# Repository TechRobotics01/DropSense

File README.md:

# DropSense
"what acctually happens when something drops"
dropsense answers that with data 

Dropsense is a wireless embedded system project which logs and transmits data in real time 
what type of data exactly?- it transmits the height from which it is dropped, the time period of the drop and the maximum Gforce which the device accelerated to during the impact .

Basically it consists of two parts the sender and the reciever 

# IMPORTANT POINT FOR THE REVIEWER
PLEASE CONSIDER THIS AS A DIGITAL DESIGN ONLY I DO NOT MEAN TO SUBMIT IT AS A IRL BUILD BUT A DIGITAL 2ND ITERATION OF THE PROJECT 
WHEN I BUILT THIS PROJECT IRL IT DID NOT WORK NOT BECAUSE IT WASN'T DESIGNED PROPERLY BUT BECAUSE AN IC FAILED AND WHICH I AM NOT ABLE TO REPLACE BECAUSE IT IS EXTREMELY COSTLY SO PLEASE CONSIDER THIS AS A DIGITAL DESIGN AND APPROVE IT 

# SENDER 
the sender consists of a custom made pcb which has a an esp32 s3 wroom 1 module an microsd card holder and a mpu6050(smd)
the sender will read the data and log it in sd card module and upomn impact that is g force greater than 5Gs then it will send info about the drop(height,time period etc) to the reciever btw this all is battery operated and it has a custom bms to power the pcb

This devise has hexagonal walls because they are better at abosrbing impacts!

# RECIEVER 
The reciever consists of an esp32 s3 wroom1 module and also an 1.8 inch tft display along with a custom made BMS for charging the battery which powers the pcb 
and the display shows all the info about the drop when it recieves the data fropm the sender 

# IRL BUILD 
## SENDER

## RECIEVER

## ZINE PAGE

# Hardware
This device consists of 
1. MPU6050
2. Esp32-S3 module (not the development board)
3. sd card module 
4. custom BMS circuit
5. A small Li-Ion batter
6. 1.8 inch tft display 

All these parts will be on a custom made PCB whcih will be be enclosed inside a 3D printed case made out of TPU (you may also use PETG or CF-NYLON for added durability)

## THIS DEVICE HAS AN ERROR OF +-1CM FOR HEIGHT WHICH IS AM EXTREMELY LOW ERROR ##

# software
This was designed using the following softwares 

1. **Fusion360** for the 3d designing of the case
2. **KiCad** for the PCB design of this device

## CONTROL LOGIC
  1. in the prototyping stage
  2. The MPU6050 reads the values at a very high speed
  3. and then the valuse are logged into the sd card in a .csv file format
  4. then for prototyping the .csv file was read and analyzed
  5. figured out the threshold values such ad the gForce values which are required for automatic triggering and logging of data
  6. for eg when the device approached near 0 gForce vaklues the device is considered in a freefall and then the mpu605 starts to log the values in the sd card module and when the impact happend and the gForce stabelized at around 1Gfprce we can consider the device is stationary again and the Esp32 enters deep sleep mode again to save battery power
  7. the .csv file can then be used to plot graphs in different types of softwares for crash analysis
  8. also the crutial values such as drop height and maximum gForce of the crashb and the time time from falling to the crash is printed on the screen of the reciever 

## APPLICATIONS 
**this device can be used and applicated in places where gForce or acceleration and decelleration needs to be preciself analyzed**
1. drone crash analysis simply mount this device onto a drone and it will automaticaklly log the data when the drone crashes 
2. it can also be used in car crash analysis
3. this device acts as a black box for analysuis 

# credits (for R&D of this device)
google.com
https://randomnerdtutorials.com/arduino-mpu-6050-accelerometer-gyroscope/
Adafruit (use for taking out the values from mpu6050)
random nerd tutorials 
grabcad for the 3d step files of the tft and micro usb

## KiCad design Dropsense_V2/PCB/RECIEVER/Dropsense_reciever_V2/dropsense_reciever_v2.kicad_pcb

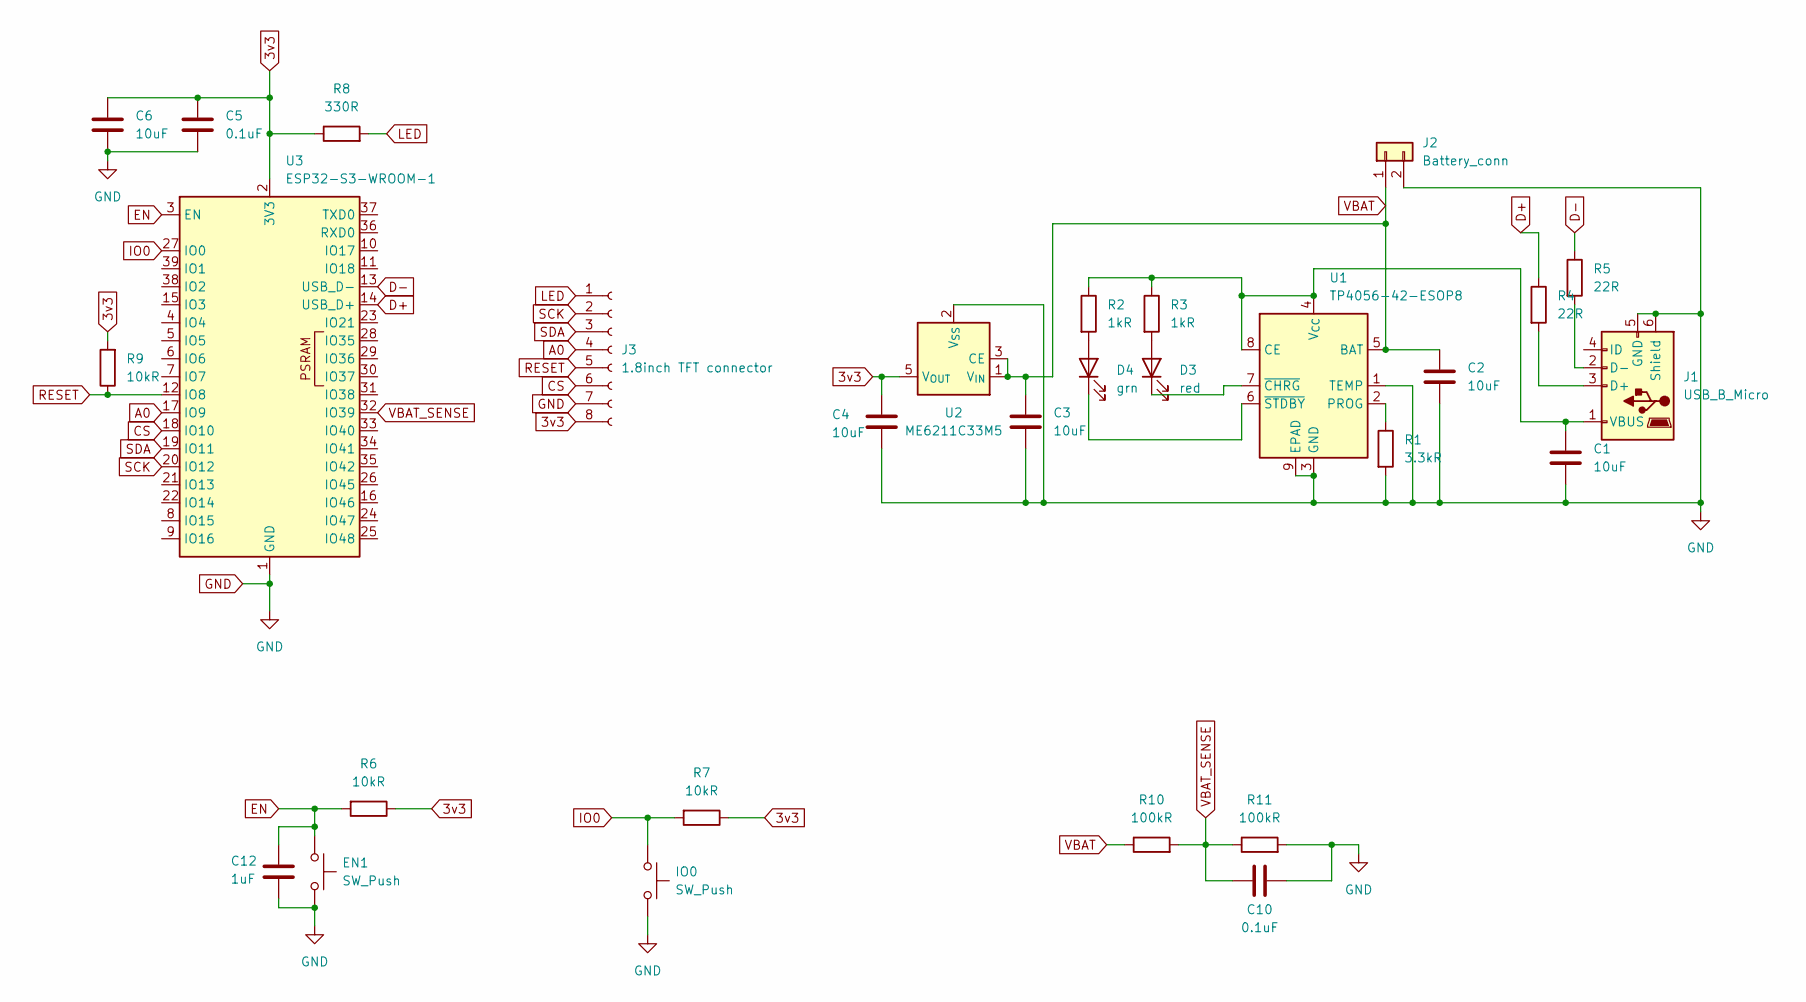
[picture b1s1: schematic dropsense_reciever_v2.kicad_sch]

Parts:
C1, C2, C3, C4, C6: 10uF; C_0805_2012Metric
C5, C10: 0.1uF; C_0805_2012Metric
C12: 1uF; C_0805_2012Metric
D3: red; LED_0805_2012Metric
D4: grn; LED_0805_2012Metric
EN1: SW_Push; SW_Push_1P1T-SH_NO_CK_KMR2xxG
IO0: SW_Push; SW_Push_1P1T-SH_NO_CK_KMR2xxG
J1: USB_B_Micro; USB_Micro-B_Amphenol_10118194-0001LF_Horizontal
J2: Battery_conn; JST_XH_B2B-XH-A_1x02_P2.50mm_Vertical
J3: 1.8inch TFT connector; PinSocket_1x08_P2.54mm_Vertical
R1: 3.3kR; R_0805_2012Metric
R2, R3: 1kR; R_0805_2012Metric
R4, R5: 22R; R_0805_2012Metric
R6, R7, R9: 10kR; R_0805_2012Metric
R8: 330R; R_0805_2012Metric
R10, R11: 100kR; R_0805_2012Metric
U1: TP4056-42-ESOP8; SOIC-8-1EP_3.9x4.9mm_P1.27mm_EP2.41x3.3mm_ThermalVias
U2: ME6211C33M5; SOT-23-5
U3: ESP32-S3-WROOM-1

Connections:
3v3: C4.1, C5.1, C6.1, J3.8, R6.1, R7.1, R8.1, R9.2, U2.5 (V_{OUT}), U3.2 (3V3)
A0: J3.4, U3.17 (IO9)
CS: J3.6, U3.18 (IO10)
D+: R4.1, U3.14 (USB_D+)
D-: R5.1, U3.13 (USB_D-)
EN: C12.1, EN1.1, R6.2, U3.3 (EN)
GND: C1.2, C2.2, C3.2, C4.2, C5.2, C6.2, C10.2, C12.2, EN1.2, IO0.2, J1.5 (GND), J1.6 (Shield), J2.2, J3.7, R1.2, R11.2, U1.1 (TEMP), U1.3 (GND), U1.9 (EPAD), U2.2 (V_{SS}), U3.1 (GND), U3.40 (GND), U3.41 (GND)
IO0: IO0.1, R7.2, U3.27 (IO0)
LED: J3.1, R8.2
unnamed: D3.2 (A), R3.2
unnamed: D3.1 (K), U1.7 (~CHRG)
unnamed: D4.2 (A), R2.2
unnamed: D4.1 (K), U1.6 (~STDBY)
unnamed: J1.3 (D+), R4.2
unnamed: J1.2 (D-), R5.2
unnamed: C1.1, J1.1 (VBUS), R2.1, R3.1, U1.4 (V_{CC}), U1.8 (CE)
unnamed: R1.1, U1.2 (PROG)
RESET: J3.5, R9.1, U3.12 (IO8)
SCK: J3.2, U3.20 (IO12)
SDA: J3.3, U3.19 (IO11)
VBAT: C2.1, C3.1, J2.1, R10.1, U1.5 (BAT), U2.1 (V_{IN}), U2.3 (CE)
VBAT_SENSE: C10.1, R10.2, R11.1, U3.32 (IO39)

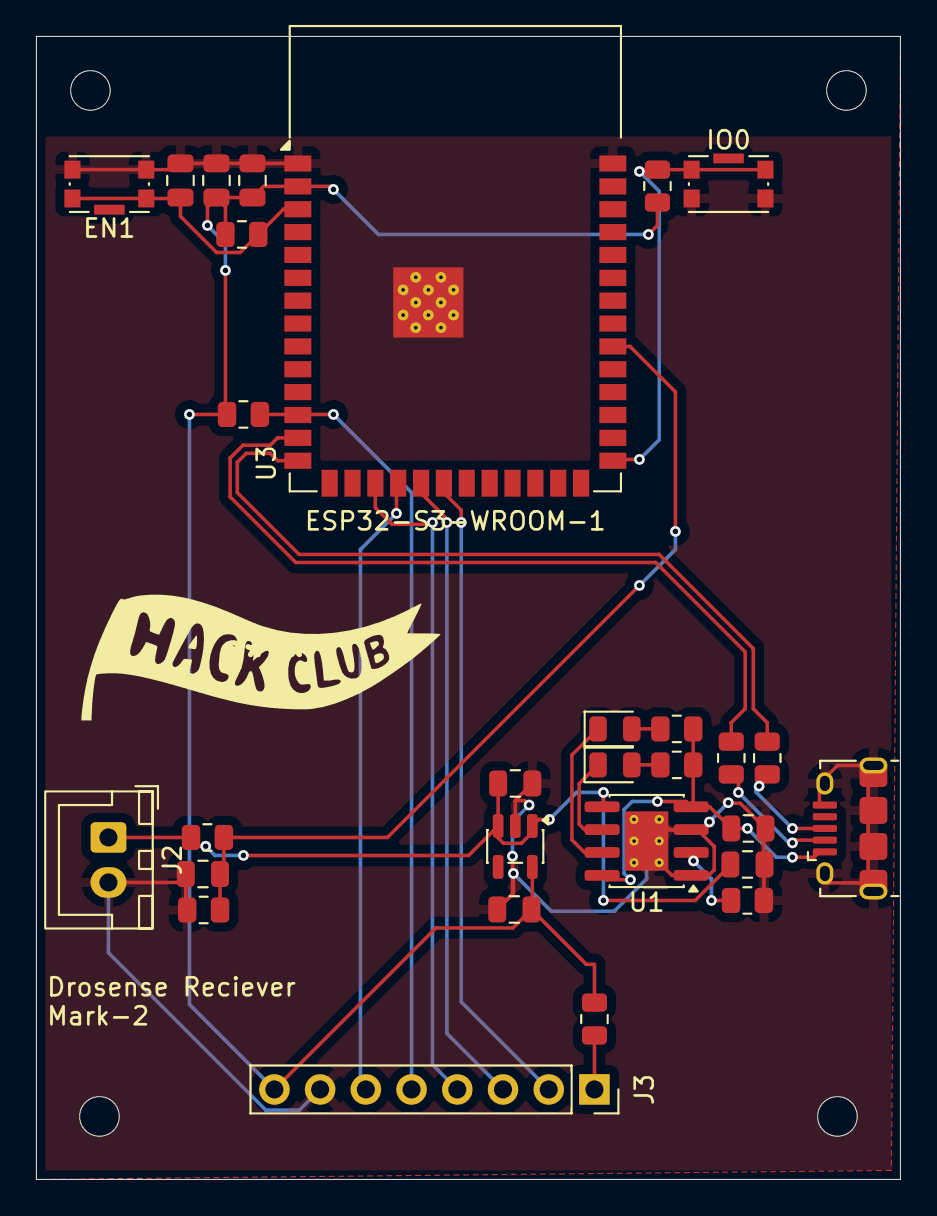
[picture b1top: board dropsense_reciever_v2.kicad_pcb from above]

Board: 2 copper layers, 48.0 x 63.5 mm, 29 parts (0 on the bottom side), 22 nets.

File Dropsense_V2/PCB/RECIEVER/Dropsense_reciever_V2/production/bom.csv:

Designator,Footprint,Quantity,Value,LCSC Part #
"C1, C2, C3, C4, C6",0805,5,10uF,
"C10, C5",0805,2,0.1uF,
C12,0805,1,1uF,
D3,0805,1,red,
D4,0805,1,grn,
"EN1, IO0",SW_Push_1P1T-SH_NO_CK_KMR2xxG,2,SW_Push,
J1,USB_Micro-B_Amphenol_10118194-0001LF_Horizontal,1,USB_B_Micro,
J2,JST_XH_B2B-XH-A_1x02_P2.50mm_Vertical,1,Battery_conn,
J3,PinSocket_1x08_P2.54mm_Vertical,1,1.8inch TFT connector,
R1,0805,1,3.3kR,
"R10, R11",0805,2,100kR,
"R2, R3",0805,2,1kR,
"R4, R5",0805,2,22R,
"R6, R7, R9",0805,3,10kR,
R8,0805,1,330R,
U1,SOIC-8-1EP_3.9x4.9mm_P1.27mm_EP2.41x3.3mm_ThermalVias,1,TP4056-42-ESOP8,
U2,SOT-23-5,1,ME6211C33M5,
U3,ESP32-S3-WROOM-1,1,ESP32-S3-WROOM-1,

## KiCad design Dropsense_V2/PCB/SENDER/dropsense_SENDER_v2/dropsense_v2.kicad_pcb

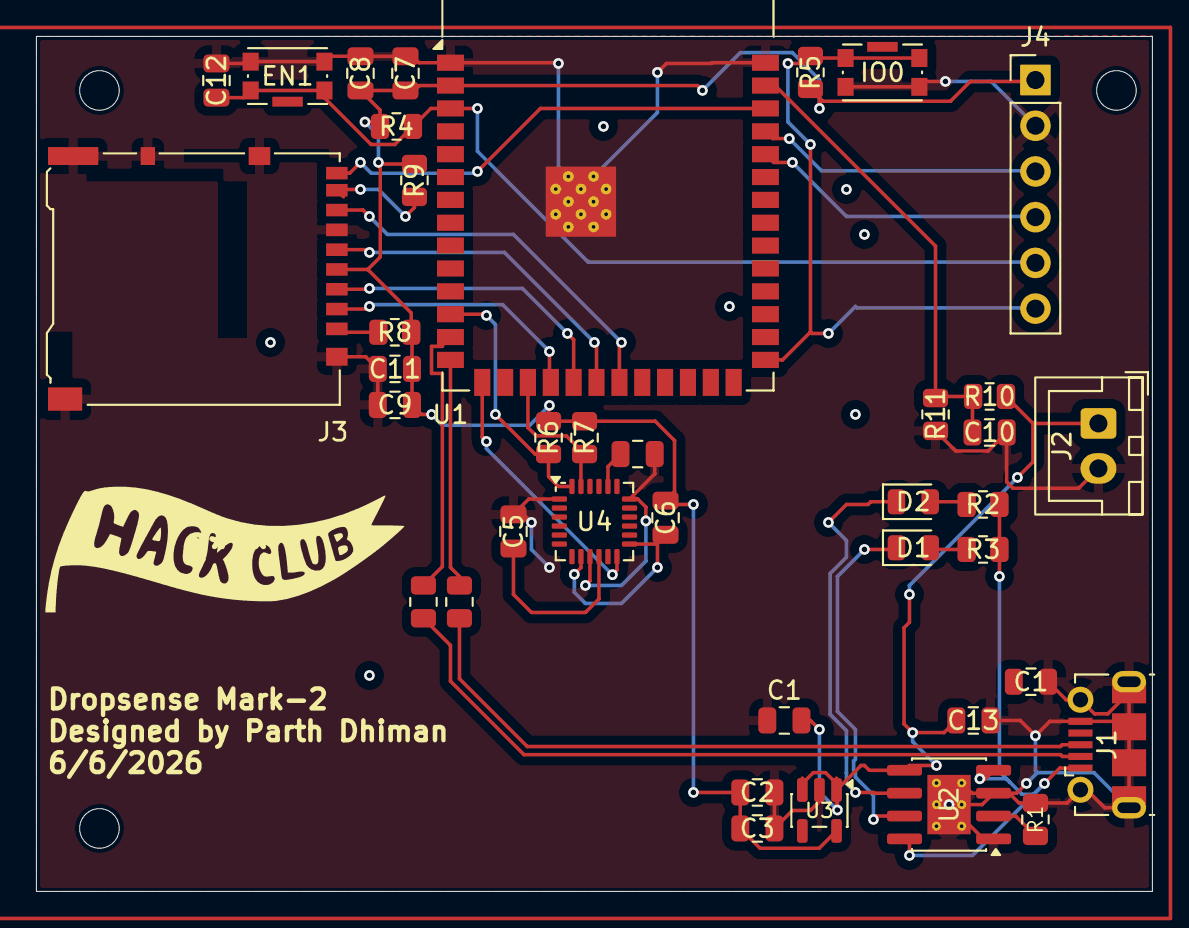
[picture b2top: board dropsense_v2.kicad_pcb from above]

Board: 2 copper layers, 62.0 x 47.5 mm, 39 parts (0 on the bottom side), 31 nets.

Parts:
C1, C1#2, C3, C8, C11, C13: 10uF; C_0805_2012Metric
C2, C6, C7, C9, C10: 0.1uF; C_0805_2012Metric
C4: 2.2nF; C_0805_2012Metric
C5: 100nF; C_0805_2012Metric
C12: 1uF; C_0805_2012Metric
D1: GREEN; LED_0805_2012Metric
D2: RED; LED_0805_2012Metric
EN1: SW_Push; SW_Push_1P1T-SH_NO_CK_KMR2xxG
IO0: SW_Push; SW_Push_1P1T-SH_NO_CK_KMR2xxG
J1: USB_B_Micro; USB_Micro-B_Molex-105017-0001
J2: Conn_01x02; JST_XH_B2B-XH-A_1x02_P2.50mm_Vertical
J3: Micro_SD_Card_Det_Hirose_DM3AT; microSD_HC_Hirose_DM3AT-SF-PEJM5
J4: Conn_01x06_Pin; PinHeader_1x06_P2.54mm_Vertical
R1: 3.3kR; R_0805_2012Metric
R2, R3: 330R; R_0805_2012Metric
R4, R5, R8, R9: 10kR; R_0805_2012Metric
R6, R7: 4.7kR; R_0805_2012Metric
R10, R11: 100kR; R_0805_2012Metric
R12, R13: 22R; R_0805_2012Metric
U1: ESP32-S3-WROOM-1
U2: TP4056-42-ESOP8; SOIC-8-1EP_3.9x4.9mm_P1.27mm_EP2.41x3.3mm_ThermalVias
U3: ME6211C33M5; SOT-23-5
U4: MPU-6050; InvenSense_QFN-24_4x4mm_P0.5mm

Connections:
3V3: C2.1, C3.1, C6.1, C7.1, C8.1, C9.1, C11.1, J3.4 (VDD), J4.1, R4.1, R5.1, R6.1, R7.1, R8.1, R9.1, U1.2 (3V3), U3.5 (V_{OUT})
D+: J1.3 (D+), R13.2
D-: J1.2 (D-), R12.2
EN: C12.1, EN1.1, J4.5, R4.2, U1.3 (EN)
GND: C1.2, C1#2.1, C2.2, C3.2, C4.2, C5.1, C7.2, C8.2, C9.2, C10.2, C11.2, C12.2, C13.2, EN1.2, IO0.2, J1.5 (GND), J1.6 (Shield), J2.2, J3.6 (VSS), J3.10 (DET_A), J3.11 (SHIELD), J4.2, R1.2, R11.2, U1.1 (GND), U1.40 (GND), U1.41 (GND), U2.1 (TEMP), U2.3 (GND), U2.9 (EPAD), U3.2 (V_{SS}), U4.1 (CLKIN), U4.9 (AD0), U4.18 (GND)
IO0: IO0.1, J4.6, R5.2, U1.27 (IO0)
MPU_INTERUPT: U1.15 (IO3), U4.12 (INT)
MPU_SCL: R7.2, U1.17 (IO9), U4.23 (SCL)
MPU_SDA: R6.2, U1.12 (IO8), U4.24 (SDA)
unnamed: D1.2 (A), R3.2
unnamed: D1.1 (K), U2.7 (~CHRG)
unnamed: D2.2 (A), R2.2
unnamed: D2.1 (K), U2.6 (~STDBY)
unnamed: J1.1 (VBUS), R2.1, R3.1, U2.4 (V_{CC}), U2.8 (CE)
unnamed: J3.8 (DAT1), R9.2
unnamed: J3.1 (DAT2), R8.2
unnamed: R13.1, U1.14 (USB_D+)
unnamed: R12.1, U1.13 (USB_D-)
unnamed: R1.1, U2.2 (PROG)
unnamed: C4.1, U4.20 (CPOUT)
unnamed: C5.2, U4.10 (REGOUT)
unnamed: C6.2, U4.8 (VLOGIC), U4.13 (VDD)
RX: J4.4, U1.36 (RXD0)
SD_CS: J3.2 (DAT3/CD), U1.18 (IO10)
SD_DETECT: J3.9 (DET_B), U1.38 (IO2)
SD_MISO: J3.7 (DAT0), U1.21 (IO13)
SD_MOSI: J3.3 (CMD), U1.19 (IO11)
SD_SCK: J3.5 (CLK), U1.20 (IO12)
TX: J4.3, U1.37 (TXD0)
VBAT: C1#2.2, C13.1, J2.1, R10.1, U2.5 (BAT), U3.1 (V_{IN}), U3.3 (CE)
VBAT_SENSE: C10.1, R10.2, R11.1, U1.39 (IO1)

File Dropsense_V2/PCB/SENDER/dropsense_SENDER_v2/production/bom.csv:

Designator,Footprint,Quantity,Value,LCSC Part #
"C1_2, C1, C11, C13, C3, C8",0805,6,10uF,
"C10, C2, C6, C7, C9",0805,5,0.1uF,
C12,0805,1,1uF,
C4,0805,1,2.2nF,
C5,0805,1,100nF,
D1,0805,1,GREEN,
D2,0805,1,RED,
"EN1, IO0",SW_Push_1P1T-SH_NO_CK_KMR2xxG,2,SW_Push,
J1,USB_Micro-B_Molex-105017-0001,1,USB_B_Micro,
J2,JST_XH_B2B-XH-A_1x02_P2.50mm_Vertical,1,Conn_01x02,
J3,microSD_HC_Hirose_DM3AT-SF-PEJM5,1,Micro_SD_Card_Det_Hirose_DM3AT,
J4,PinHeader_1x06_P2.54mm_Vertical,1,Conn_01x06_Pin,
R1,0805,1,3.3kR,
"R10, R11",0805,2,100kR,
"R12, R13",0805,2,22R,
"R2, R3",0805,2,330R,
"R4, R5, R8, R9",0805,4,10kR,
"R6, R7",0805,2,4.7kR,
U1,ESP32-S3-WROOM-1,1,ESP32-S3-WROOM-1,
U2,SOIC-8-1EP_3.9x4.9mm_P1.27mm_EP2.41x3.3mm_ThermalVias,1,TP4056-42-ESOP8,
U3,SOT-23-5,1,ME6211C33M5,
U4,InvenSense_QFN-24_4x4mm_P0.5mm,1,MPU-6050,

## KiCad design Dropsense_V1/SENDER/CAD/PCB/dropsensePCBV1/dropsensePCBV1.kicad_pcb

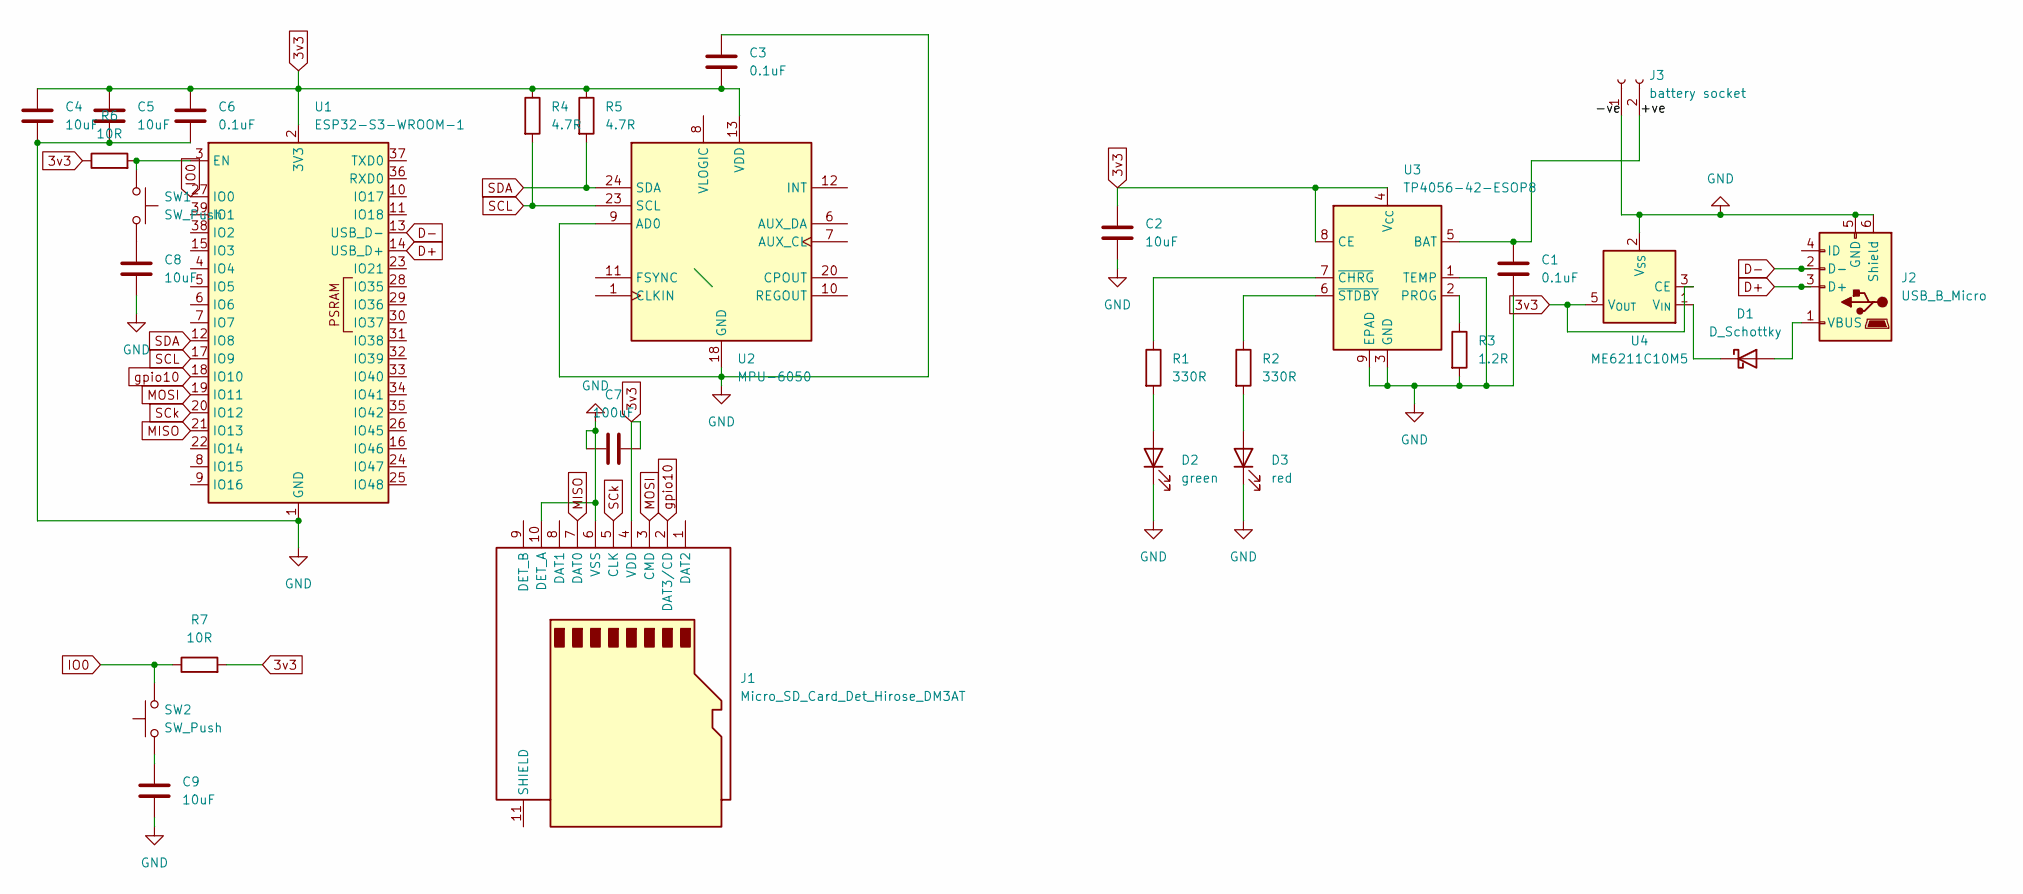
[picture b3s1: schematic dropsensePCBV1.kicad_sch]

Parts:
C1, C3, C6: 0.1uF; C_0805_2012Metric
C2, C4, C5, C8, C9: 10uF; C_0805_2012Metric
C7: 100uF; C_0805_2012Metric
D1: D_Schottky; D_0805_2012Metric
D2: green; LED_0805_2012Metric
D3: red; LED_0805_2012Metric
J1: Micro_SD_Card_Det_Hirose_DM3AT; microSD_HC_Hirose_DM3AT-SF-PEJM5
J2: USB_B_Micro; USB_Micro-B_Amphenol_10103594-0001LF_Horizontal
J3: battery socket; JST_PH_B2B-PH-K_1x02_P2.00mm_Vertical
R1, R2: 330R; R_0805_2012Metric
R3: 1.2R; R_0805_2012Metric
R4, R5: 4.7R; R_0805_2012Metric
R6, R7: 10R; R_0805_2012Metric
SW1, SW2: SW_Push; SW_PUSH_6mm_H4.3mm
U1: ESP32-S3-WROOM-1
U2: MPU-6050; InvenSense_QFN-24_4x4mm_P0.5mm
U3: TP4056-42-ESOP8; SOIC-8-1EP_3.9x4.9mm_P1.27mm_EP2.41x3.3mm_ThermalVias
U4: ME6211C10M5; SOT-23-5

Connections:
3v3: C2.1, C3.2, C4.1, C5.1, C6.1, C7.2, J1.4 (VDD), R4.1, R5.1, R6.1, R7.2, U1.2 (3V3), U2.13 (VDD), U3.4 (V_{CC}), U3.8 (CE), U4.3 (CE), U4.5 (V_{OUT}); also elsewhere on the board
/+ve: C1.1, J3.2, U3.5 (BAT)
D+: J2.3 (D+), U1.14 (USB_D+)
D-: J2.2 (D-), U1.13 (USB_D-)
GND: C1.2, C2.2, C3.1, C4.2, C5.2, C6.2, C7.1, C8.2, C9.2, D2.1 (K), D3.1 (K), J1.6 (VSS), J1.10 (DET_A), J2.5 (GND), J2.6 (Shield), J3.1, R3.2, U1.1 (GND), U1.40 (GND), U1.41 (GND), U2.9 (AD0), U2.18 (GND), U3.1 (TEMP), U3.3 (GND), U3.9 (EPAD), U4.2 (V_{SS}); also elsewhere on the board
IO0: R7.1, SW2.2, U1.27 (IO0)
MISO: J1.7 (DAT0), U1.21 (IO13)
MOSI: J1.3 (CMD), U1.19 (IO11)
unnamed: C8.1, SW1.2
unnamed: C9.1, SW2.1
unnamed: D1.2 (A), J2.1 (VBUS)
unnamed: D1.1 (K), U4.1 (V_{IN})
unnamed: D2.2 (A), R1.2
unnamed: D3.2 (A), R2.2
unnamed: R6.2, SW1.1, U1.3 (EN)
unnamed: R3.1, U3.2 (PROG)
unnamed: R1.1, U3.7 (~CHRG)
unnamed: R2.1, U3.6 (~STDBY)
SCL: R4.2, U1.17 (IO9), U2.23 (SCL); also elsewhere on the board
SCk: J1.5 (CLK), U1.20 (IO12)
SDA: R5.2, U1.12 (IO8), U2.24 (SDA); also elsewhere on the board
gpio10: J1.2 (DAT3/CD), U1.18 (IO10)

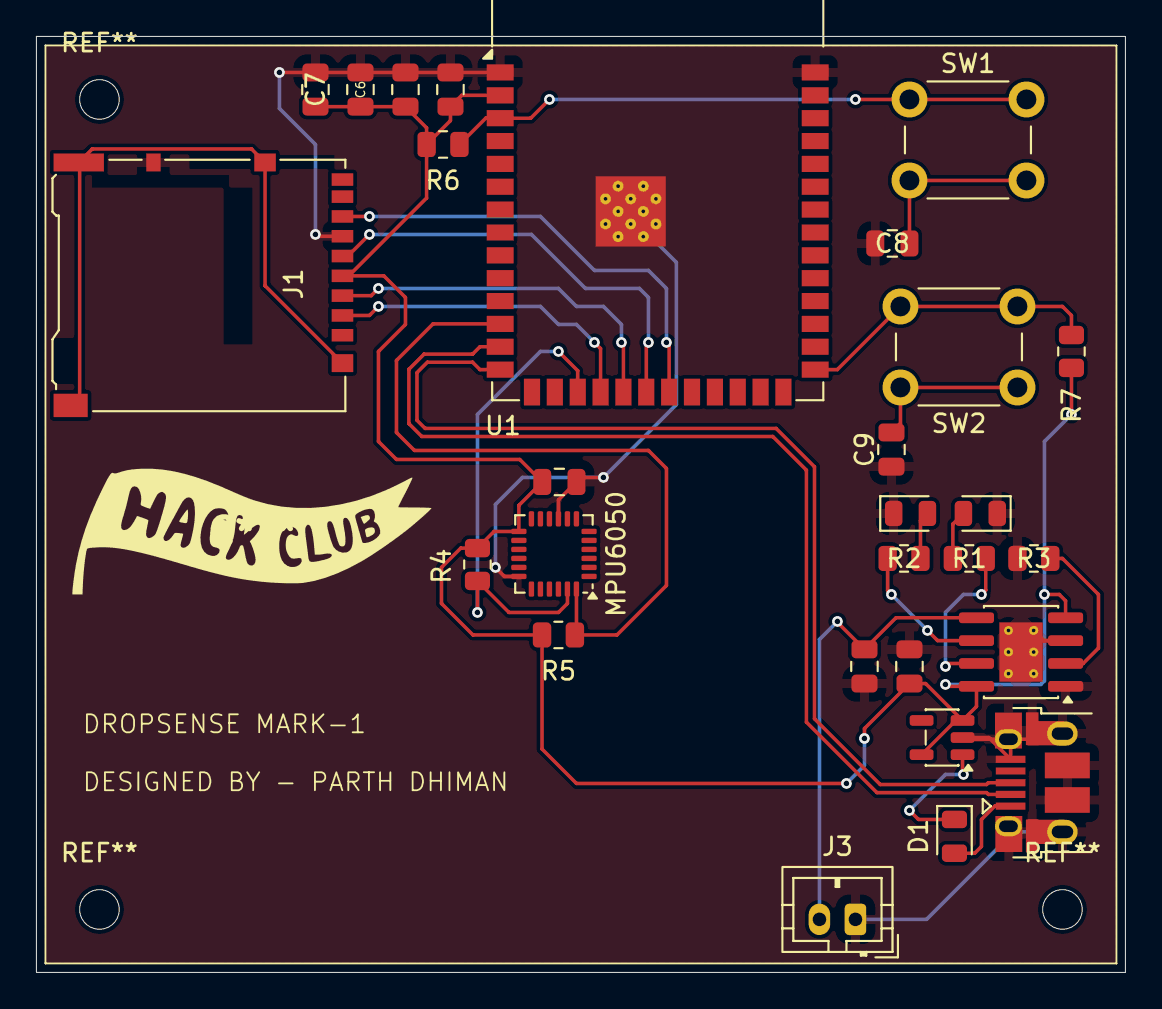
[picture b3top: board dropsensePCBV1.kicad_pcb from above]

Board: 2 copper layers, 60.5 x 52.0 mm, 28 parts (0 on the bottom side), 22 nets.

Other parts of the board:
MPU6050: MPU-6050; InvenSense_QFN-24_4x4mm_P0.5mm

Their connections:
3v3: MPU6050.13 (VDD); also elsewhere on the board
GND: MPU6050.9 (AD0), MPU6050.18 (GND); also elsewhere on the board
SCL: MPU6050.23 (SCL); also elsewhere on the board
SDA: MPU6050.24 (SDA); also elsewhere on the board

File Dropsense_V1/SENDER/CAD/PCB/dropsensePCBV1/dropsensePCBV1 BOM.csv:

"Reference","Qty","Value","DNP","Exclude from BOM","Exclude from Board","Footprint","Datasheet"
"C1,C3,C6","3","0.1uF","","","","Capacitor_SMD:C_0805_2012Metric","~"
"C2,C4,C5,C8,C9","5","10uF","","","","Capacitor_SMD:C_0805_2012Metric","~"
"C7","1","100uF","","","","Capacitor_SMD:C_0805_2012Metric","~"
"D1","1","D_Schottky","","","","Diode_SMD:D_0805_2012Metric","~"
"D2","1","green","","","","LED_SMD:LED_0805_2012Metric","~"
"D3","1","red","","","","LED_SMD:LED_0805_2012Metric","~"
"J1","1","Micro_SD_Card_Det_Hirose_DM3AT","","","","Connector_Card:microSD_HC_Hirose_DM3AT-SF-PEJM5","https://www.hirose.com/product/en/download_file/key_name/DM3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"
"J2","1","USB_B_Micro","","","","Connector_USB:USB_Micro-B_Amphenol_10103594-0001LF_Horizontal","~"
"J3","1","battery socket","","","","Connector_JST:JST_PH_B2B-PH-K_1x02_P2.00mm_Vertical","~"
"R1,R2","2","330R","","","","Resistor_SMD:R_0805_2012Metric","~"
"R3","1","1.2R","","","","Resistor_SMD:R_0805_2012Metric","~"
"R4,R5","2","4.7R","","","","Resistor_SMD:R_0805_2012Metric","~"
"R6,R7","2","10R","","","","Resistor_SMD:R_0805_2012Metric","~"
"SW1,SW2","2","SW_Push","","","","Button_Switch_THT:SW_PUSH_6mm_H4.3mm","~"
"U1","1","ESP32-S3-WROOM-1","","","","RF_Module:ESP32-S3-WROOM-1","https://www.espressif.com/sites/default/files/documentation/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"
"U2","1","MPU-6050","","","","Sensor_Motion:InvenSense_QFN-24_4x4mm_P0.5mm","https://invensense.tdk.com/wp-content/uploads/2015/02/MPU-60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"
"U3","1","TP4056-42-ESOP8","","","","Package_SO:SOIC-8-1EP_3.9x4.9mm_P1.27mm_EP2.41x3.3mm_ThermalVias","https://www.lcsc.com/datasheet/lcsc_datasheet_2410121619_TOP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"
"U4","1","ME6211C10M5","","","","Package_TO_SOT_SMD:SOT-23-5","https://www.lcsc.com/datasheet/lcsc_datasheet_2304140030_MIC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"

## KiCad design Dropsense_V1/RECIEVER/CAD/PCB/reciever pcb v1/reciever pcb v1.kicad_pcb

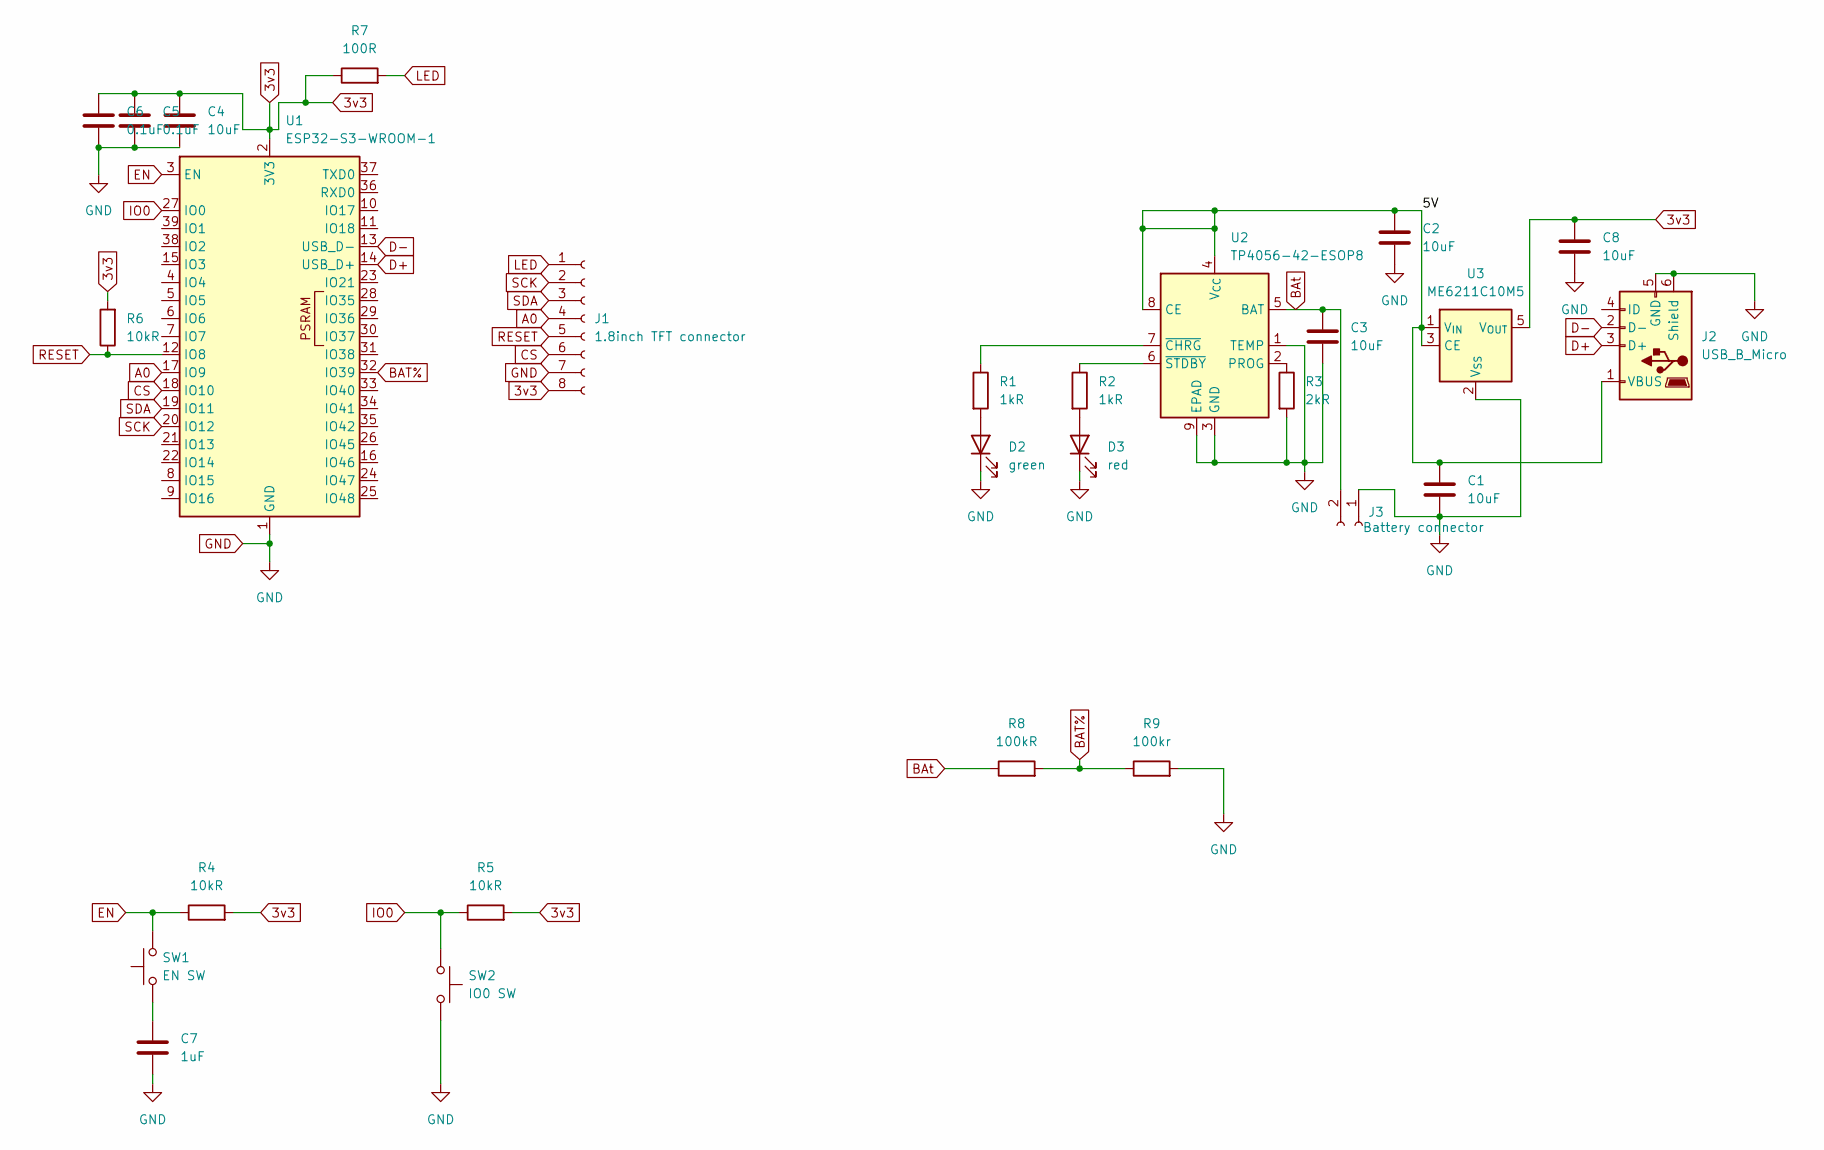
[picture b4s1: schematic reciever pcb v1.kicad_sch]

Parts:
C1, C2, C3, C4, C8: 10uF; C_0805_2012Metric
C5, C6: 0.1uF; C_0805_2012Metric
C7: 1uF; C_0805_2012Metric
D2: green; LED_0805_2012Metric
D3: red; LED_0805_2012Metric
J1: 1.8inch TFT connector; PinSocket_1x08_P2.54mm_Vertical
J2: USB_B_Micro; USB_Micro-B_Technik_TWP-4002D-H3
J3: Battery connector; JST_XH_S2B-XH-A_1x02_P2.50mm_Horizontal
R1, R2: 1kR; R_0805_2012Metric
R3: 2kR; R_0805_2012Metric
R4, R5, R6: 10kR; R_0805_2012Metric
R7: 100R; R_0805_2012Metric
R8: 100kR; R_0805_2012Metric
R9: 100kr; R_0805_2012Metric
SW1: EN SW; SW_PUSH_6mm_H4.3mm
SW2: IO0 SW; SW_PUSH_6mm_H4.3mm
U1: ESP32-S3-WROOM-1
U2: TP4056-42-ESOP8; SOIC-8-1EP_3.9x4.9mm_P1.27mm_EP2.41x3.3mm_ThermalVias
U3: ME6211C10M5; SOT-23-5

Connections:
3v3: C4.1, C5.1, C6.1, C8.1, J1.8, R4.2, R5.2, R6.2, R7.1, U1.2 (3V3), U3.5 (V_{OUT}); also elsewhere on the board
/5V: C1.1, C2.1, J2.1 (VBUS), U2.4 (V_{CC}), U2.8 (CE), U3.1 (V_{IN}), U3.3 (CE)
A0: J1.4, U1.17 (IO9)
BAT%: R8.2, R9.1, U1.32 (IO39)
BAt: C3.1, J3.2, R8.1, U2.5 (BAT)
CS: J1.6, U1.18 (IO10)
D+: J2.3 (D+), U1.14 (USB_D+)
D-: J2.2 (D-), U1.13 (USB_D-)
EN: R4.1, SW1.2, U1.3 (EN); also elsewhere on the board
GND: C1.2, C2.2, C3.2, C4.2, C5.2, C6.2, C7.2, C8.2, D2.1 (K), D3.1 (K), J1.7, J2.5 (GND), J2.6 (Shield), J3.1, R3.2, R9.2, SW2.2, U1.1 (GND), U1.40 (GND), U1.41 (GND), U2.1 (TEMP), U2.3 (GND), U2.9 (EPAD), U3.2 (V_{SS})
IO0: R5.1, SW2.1, U1.27 (IO0)
LED: J1.1, R7.2
unnamed: C7.1, SW1.1
unnamed: D2.2 (A), R1.2
unnamed: D3.2 (A), R2.2
unnamed: R3.1, U2.2 (PROG)
unnamed: R1.1, U2.7 (~CHRG)
unnamed: R2.1, U2.6 (~STDBY)
RESET: J1.5, R6.1, U1.12 (IO8)
SCK: J1.2, U1.20 (IO12)
SDA: J1.3, U1.19 (IO11)

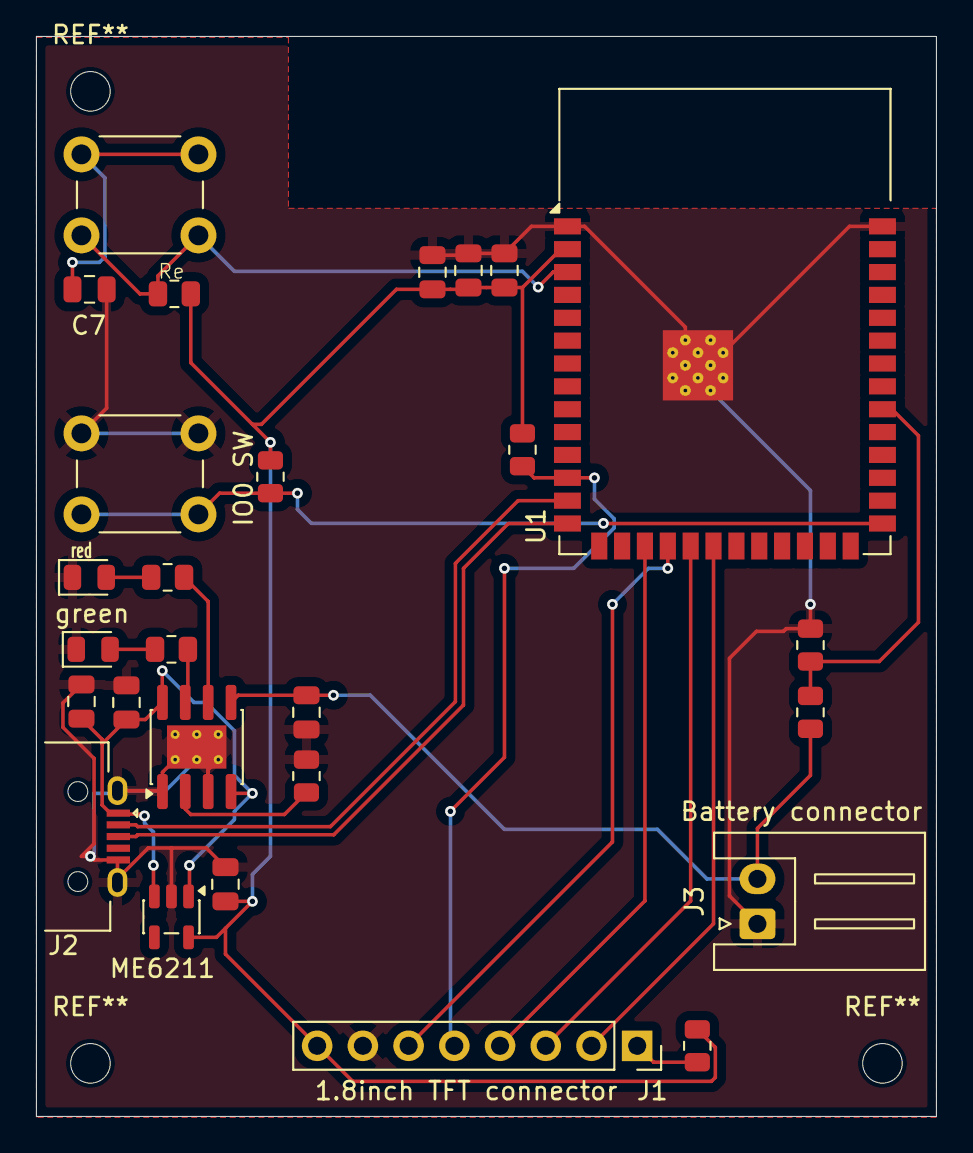
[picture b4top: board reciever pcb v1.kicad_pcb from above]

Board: 2 copper layers, 50.0 x 60.0 mm, 27 parts (0 on the bottom side), 21 nets.

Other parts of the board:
Re: 10kR; R_0805_2012Metric

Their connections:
3v3: Re.2; also elsewhere on the board
EN: Re.1; also elsewhere on the board

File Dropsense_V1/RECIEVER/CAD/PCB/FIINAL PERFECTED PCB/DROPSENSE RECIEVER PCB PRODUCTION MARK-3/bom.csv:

Designator,Footprint,Quantity,Value,LCSC Part #
"C1, C2, C3, C4, C8",0805,5,10uF,
"C5, C6",0805,2,0.1uF,
C7,0805,1,1uF,
D2,0805,1,green,
D3,0805,1,red,
J1,PinSocket_1x08_P2.54mm_Vertical,1,1.8inch TFT connector,
J2,USB_Micro-B_Technik_TWP-4002D-H3,1,USB_B_Micro,
J3,JST_XH_S2B-XH-A_1x02_P2.50mm_Horizontal,1,Battery connector,
"R1, R2",0805,2,1kR,
R3,0805,1,2kR,
"R5, R6, RE",0805,3,10kR,
R7,0805,1,100R,
"R8, R9",0805,2,100kR,
SW1,SW_PUSH_6mm_H4.3mm,1,EN SW,
SW2,SW_PUSH_6mm_H4.3mm,1,IO0 SW,
U1,ESP32-S3-WROOM-1,1,ESP32-S3-WROOM-1,
U2,SOIC-8-1EP_3.9x4.9mm_P1.27mm_EP2.41x3.3mm_ThermalVias,1,TP4056,
U3,SOT-23-5,1,ME6211,

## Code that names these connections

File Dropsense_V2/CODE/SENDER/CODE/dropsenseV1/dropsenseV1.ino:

#include <Adafruit_MPU6050.h>
#include <Wire.h>
#include <SPI.h>
#include <SD.h>
#include "WiFi.h"
#include <esp_now.h>

// Pin Definitions according to Schematic
const int SD_CS_PIN   = 10;
const int SD_MOSI_PIN = 11;
const int SD_SCK_PIN  = 12;
const int SD_MISO_PIN = 13;

const int SDA_PIN     = 8;
const int SCL_PIN     = 9;

uint8_t broadcastAddress[] = {0xC8, 0x2E, 0x18, 0xF7, 0x8F, 0xAC};

Adafruit_MPU6050 mpu;
Adafruit_Sensor *mpu_ax, *mpu_gr;

File droplog; 

float fallTime = 0;  
float height = 0;
float maxG = 0;
float gForce = 0;

bool fall = false;
bool isStatic = true;
bool impt = false;

String event = "stat";

unsigned long fallstart = 0;
unsigned long impact = 0;

typedef struct struct_message  {
  float falltime1;
  float height1;
  float maxG1;
  float gForce1; 

} struct_message;

struct_message dropdat;

esp_now_peer_info_t peerInfo;


void setup() {
  Serial.begin(115200);
  WiFi.mode(WIFI_STA);
  Serial.println(WiFi.macAddress());

  if (esp_now_init() != ESP_OK){
    Serial.println("Error initializing esp-now");
    return;
  }

  esp_now_register_send_cb(senddata);

  memcpy(peerInfo.peer_addr, broadcastAddress, 6);
  peerInfo.channel = 0;
  peerInfo.encrypt = false;

  if (esp_now_add_peer(&peerInfo) != ESP_OK){
    Serial.println("Failed to add peer");
    return;
  }

  while (!Serial) delay(10);

  Serial.println("MPU6050 + SD test");

  // Initialize custom I2C pins (SDA = 8, SCL = 9)
  Wire.begin(SDA_PIN, SCL_PIN);

  if (!mpu.begin(0x68, &Wire)) {
    Serial.println("Failed to find MPU6050 chip");
    while (1) delay(10);
  }

  Serial.println("MPU6050 Found!");

  mpu.setAccelerometerRange(MPU6050_RANGE_16_G);

  mpu_ax = mpu.getAccelerometerSensor();
  mpu_gr = mpu.getGyroSensor();

  mpu_ax->printSensorDetails();
  mpu_gr->printSensorDetails();

  // Initialize custom SPI pins for SD card
  SPI.begin(SD_SCK_PIN, SD_MISO_PIN, SD_MOSI_PIN, SD_CS_PIN);

  if (!SD.begin(SD_CS_PIN)) {
    Serial.println("SD init failed!");
    while (1);
  }

  Serial.println("SD ready!");

  droplog = SD.open("/droplog.csv", FILE_WRITE);

  if (droplog) {
    droplog.println("time,gForce,event");
    droplog.close();
  }
}

void loop() {

  readmpu();
  status();
  hndlimpt();
  logdata();

  delay(1);
}

void readmpu(){
  sensors_event_t ax;
  sensors_event_t gr;

  mpu_ax->getEvent(&ax);
  mpu_gr->getEvent(&gr);

  float ax_val = ax.acceleration.x;
  float ay_val = ax.acceleration.y;
  float az_val = ax.acceleration.z;

  float rawG = sqrt(ax_val * ax_val + ay_val * ay_val + az_val * az_val) / 9.81;

  gForce = rawG;

  if(rawG > maxG){
    maxG = rawG;
  }
}

void status(){
  if (gForce < 0.30 && gForce > 0 && !fall) {
    fall = true;
    isStatic = false;
    impt = false;
    event = "fall";
  }

  else if (gForce > 0.85 && gForce < 1.5) {
    fall = false;
    isStatic = true;
    impt = false;
    event = "stat";
  }

  else if (gForce > 5 && fall) {  
    impt = true;
    event = "impt";
  }
}

void hndlimpt(){
  static bool fallstarted = false;
  static bool impactdetected = false;

  if (fall && !fallstarted){
    fallstarted = true;
    fallstart = millis();
    Serial.println("FALLING...");
  }

  else if (impt && !impactdetected){
    impactdetected = true;
    impact = millis();
    Serial.println("IMPACT DETECTED!!!");

    fallTime = (impact - fallstart) / 1000.0;
    height = 0.5 * 9.8 * fallTime * fallTime;
    height *= 1.3;   

    Serial.print("TIME PERIOD = ");
    Serial.println(fallTime);

    Serial.print("HEIGHT = ");
    Serial.println(height);

    Serial.print("PEAK GFORCE = ");   
    Serial.println(maxG);

    setdatstosend();

  }

  if (impt){
    delay(2000);

    maxG = 0;   

    fall = false;
    impt = false;
    event = "stat";

    fallstarted = false;
    impactdetected = false;
  }
}

void logdata(){ 
  droplog = SD.open("/droplog.csv", FILE_APPEND); 

  if (droplog) {
    droplog.print(millis());
    droplog.print(",");
    droplog.print(gForce);
    droplog.print(",");
    droplog.println(event);
    droplog.close();
  }
}

void smoothGForce() {
  static float prevG = 0;   
  float alpha = 0.7;

  gForce = alpha * prevG + (1 - alpha) * gForce;
  prevG = gForce;
}

void senddata(const wifi_tx_info_t *info, esp_now_send_status_t status){
  Serial.print("data sent");
  Serial.println(status == ESP_NOW_SEND_SUCCESS ? "DELIVERY SUCCESS" : "DELIVERY FAIL");
}

void setdatstosend(){
  dropdat.falltime1 = fallTime;
  dropdat.height1 = height;
  dropdat.maxG1 = maxG;
  dropdat.gForce1 = gForce;

  esp_err_t result = esp_now_send(broadcastAddress, (uint8_t *)
   &dropdat, sizeof(dropdat));

   if(result == ESP_OK){
    Serial.print("sent with success");
   }

   else{
    Serial.println("error sending dats");
   }
  delay(10);
}

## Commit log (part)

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2026-03-23 Update README.md
    added more info in readme about the project
2026-03-24 Code V2
    updated the code improved the functionality better variable names
    added sd card functioanlity
2026-03-24 added wiring.csv file
2026-03-25 started rough pcb design
2026-03-25 Update WIRING DIGRAMS (for prototype).csv
    added guide to open the file in microsoft excel for proper viewing
2026-03-25 STARTED PCB SCHEMATICS WORK
    started pcb schematics work and finished the schematics
2026-03-25 Update README.md
    added more detail for the V1
2026-03-25 saved pcb files in device
2026-03-25 PCB DESIGN OF DROPSENSE V1 COMPLETED
2026-03-25 UPDATED DROPSENSE PCB
2026-03-26 updated code synatx
2026-03-26 dropsense v1 code perfected
2026-03-27 development of dropsense reciever code
2026-03-27 created reciever pcv v1
2026-03-28 Routed and finished reciever pcb
2026-03-29 PCB improvement
    updated and polished both the pcbs of the sender and reciever mainly woked on moving viases away from smd components
2026-03-30 made the 3d design and assembly
    made the 3d design and assembly for dropsense reciever
2026-03-30 3d design of sender enclosure started
2026-03-31 updated 3d designs and BOM
2026-04-01 UPDATED AND PERFECTED bom FILE
2026-04-01 made the zine page
    rendered the designs and made the zine page
2026-04-01 updated BOM
2026-04-01 UPDATED BOM
    (final bom)
2026-04-23 update!
2026-06-03 updated PCB files
2026-06-05 STARTED DROPSENSE V2!!!!!!
2026-06-05 updates for pcb dropsense v2
2026-06-08 started work on dropsense sender and reciever new pcb
2026-06-09 made dropsense reciever pcb
2026-06-09 step files
2026-06-13 denesting stuff
